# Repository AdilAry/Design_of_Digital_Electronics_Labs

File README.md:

Project for a long range transmitter / reciever.

---
### PCB design requirements;

- No 90 degree trace angles.

- Ground net connected to the copper pour.

- 2 side PCB with several vias connecting them.

- 1 mm and 0.8 mm(in areas where a potential clearence issue might arise.) trace width for the power line.   

- PCB should fit within the Eurocard standard margins 100mm x 160mm.

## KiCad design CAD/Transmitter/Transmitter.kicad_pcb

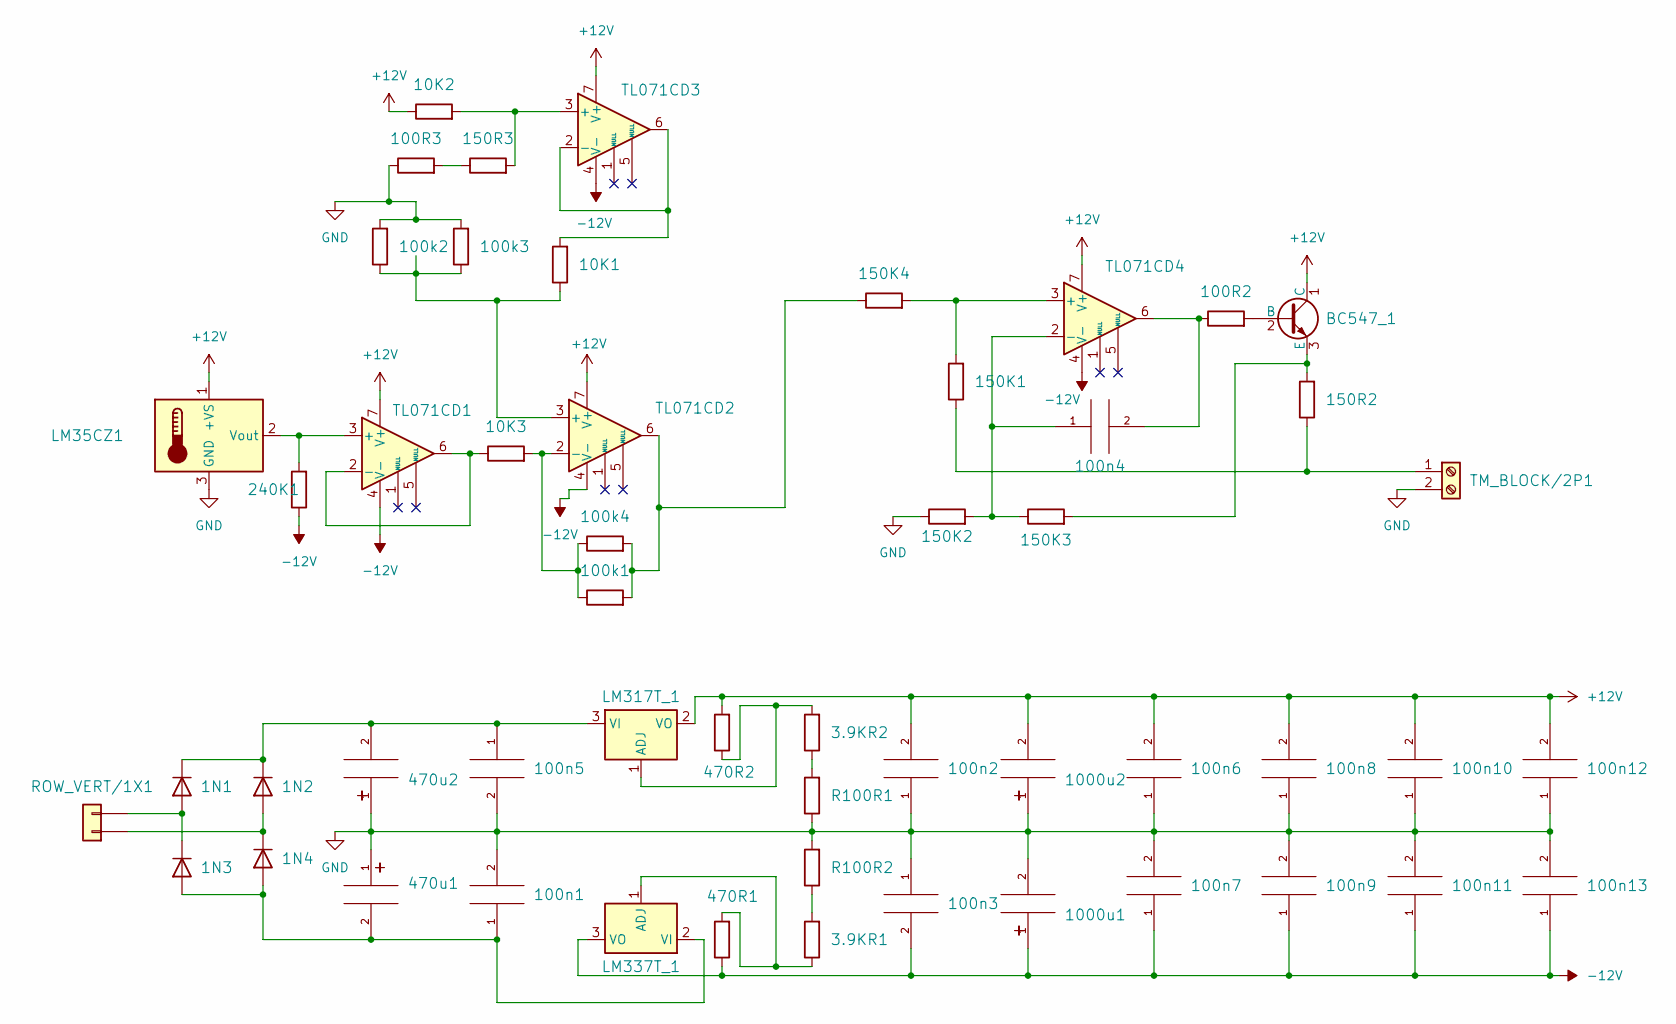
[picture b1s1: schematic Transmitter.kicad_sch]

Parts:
1N1, 1N2, 1N3, 1N4: 1N4007; DO41; Voltage Rating 1000V
3.9KR1, 3.9KR2: 3.9k; 1206; Tolerance +-5%
10K1, 10K2, 10K3: 10k; 1206; Tolerance +-5%
100R2, 100R3: 100R; 1206; Tolerance +-5%
100k1, 100k2, 100k3, 100k4: 100k; 1206; Tolerance +-5%
100n1, 100n2, 100n3, 100n4, 100n5, 100n6, 100n7, 100n8, 100n9, 100n10, 100n11, 100n12, 100n13: 100NF_50V_CER; C1206; Tolerance +-10%
150K1, 150K2, 150K3, 150K4: 150k; 1206; Tolerance +-5%
150R2, 150R3: 150R; 1206; Tolerance +-5%
240K1: 240k; R3_5W; Tolerance +-1%
470R1, 470R2: 470R; 1206; Tolerance +-5%
470u1, 470u2: 470UF_50V_ELE; C_P_5_0_13; Tolerance +-20%
1000u1, 1000u2: 1000UF_50V_ELE; C_P_5_0_13; Tolerance +-20%
BC547_1: BC547_TO92_0.1A; TO-92
LM35CZ1: LM35CZ_TO92; TO-92
LM317T_1: LM317T_TO220_1.5A; TO-220
LM337T_1: LM337T_TO220_1.5A; TO-220
R100R1, R100R2: 100R; 1206; Tolerance +-5%
ROW_VERT/1X1: ROW_VERT_1X2; ROW_VERT_1x2
TL071CD1, TL071CD2, TL071CD3, TL071CD4: TL071CD_SO8; SO8IC
TM_BLOCK/2P1: TM_BLOCK_2P

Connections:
+12V: 10K2.1, 100n2.2, 100n6.2, 100n8.2, 100n10.2, 100n12.2, 470R2.2, 1000u2.2, BC547_1.1 (C), LM35CZ1.1 (+VS), LM317T_1.2 (VO), TL071CD1.7 (V+), TL071CD2.7 (V+), TL071CD3.7 (V+), TL071CD4.7 (V+)
-12V: 100n3.2, 100n7.1, 100n9.1, 100n11.1, 100n13.1, 240K1.1, 470R1.1, 1000u1.1, LM337T_1.3 (VO), TL071CD1.4 (V-), TL071CD2.4 (V-), TL071CD3.4 (V-), TL071CD4.4 (V-)
GND: 100R3.1, 100k2.2, 100k3.2, 100n1.2, 100n2.1, 100n3.1, 100n5.2, 100n6.1, 100n7.2, 100n8.1, 100n9.2, 100n10.1, 100n11.2, 100n12.1, 100n13.2, 150K2.1, 470u1.1, 470u2.1, 1000u1.2, 1000u2.1, LM35CZ1.3 (GND), R100R1.1, R100R2.2, TM_BLOCK/2P1.2
unnamed: 1N1.2 (A), 1N3.1 (K), ROW_VERT/1X1.2
unnamed: 1N1.1 (K), 1N2.1 (K), 100n5.1, 470u2.2, LM317T_1.3 (VI)
unnamed: 1N2.2 (A), 1N4.1 (K), ROW_VERT/1X1.1
unnamed: 1N3.2 (A), 1N4.2 (A), 100n1.1, 470u1.2, LM337T_1.2 (VI)
unnamed: 3.9KR1.2, R100R2.1
unnamed: 3.9KR2.1, R100R1.2
unnamed: 100R2.1, 100n4.2, TL071CD4.6
unnamed: 100R3.2, 150R3.1
unnamed: 100k1.2, 100k4.2, 150K4.1, TL071CD2.6
unnamed: 100R2.2, BC547_1.2 (B)
unnamed: 150K3.2, 150R2.2, BC547_1.3 (E)
unnamed: 240K1.2, LM35CZ1.2 (Vout), TL071CD1.3 (+)
unnamed: 3.9KR2.2, 470R2.1, LM317T_1.1 (ADJ)
unnamed: 3.9KR1.1, 470R1.2, LM337T_1.1 (ADJ)
unnamed: 10K3.1, TL071CD1.2 (-), TL071CD1.6
unnamed: 10K1.1, 100k2.1, 100k3.1, TL071CD2.3 (+)
unnamed: 10K3.2, 100k1.1, 100k4.1, TL071CD2.2 (-)
unnamed: 10K2.2, 150R3.2, TL071CD3.3 (+)
unnamed: 10K1.2, TL071CD3.2 (-), TL071CD3.6
unnamed: 150K1.2, 150K4.2, TL071CD4.3 (+)
unnamed: 100n4.1, 150K2.2, 150K3.1, TL071CD4.2 (-)
unnamed: 150K1.1, 150R2.1, TM_BLOCK/2P1.1

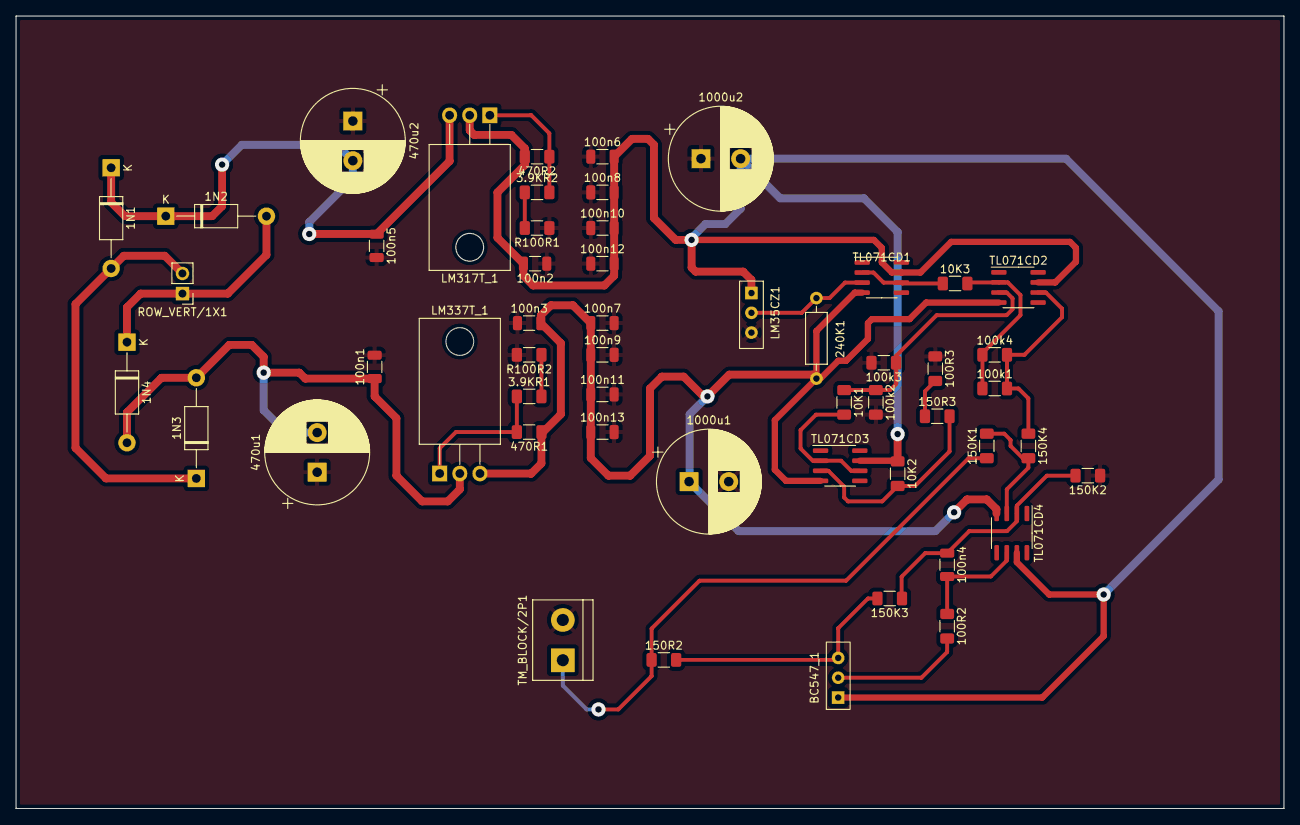
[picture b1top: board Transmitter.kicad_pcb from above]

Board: 2 copper layers, 160.0 x 100.0 mm, 53 parts (0 on the bottom side), 25 nets.

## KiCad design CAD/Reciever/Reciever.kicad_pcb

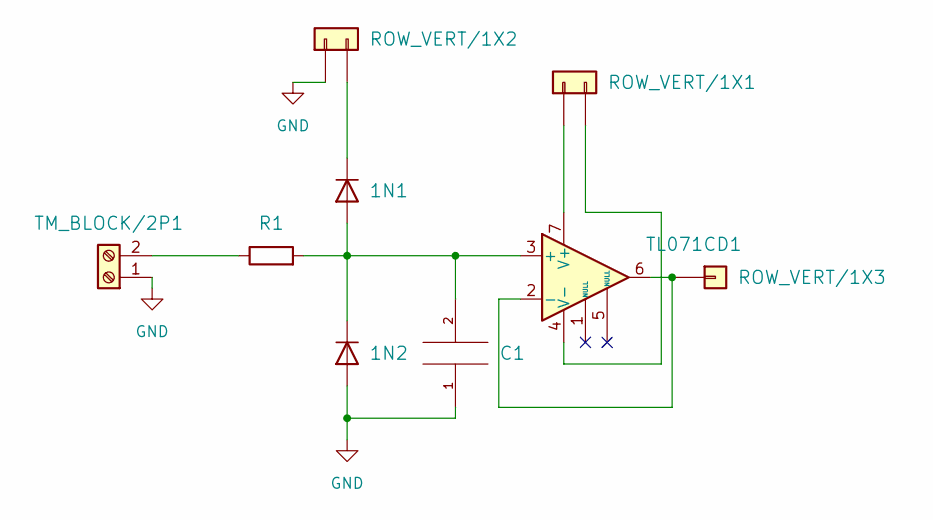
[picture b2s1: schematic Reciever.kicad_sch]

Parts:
1N1, 1N2: 1N4148; DO41; Voltage Rating 75V
C1: 10NF_50V_CER; C1206; Tolerance +-10%
R1: 100R; 1206; Tolerance +-5%
ROW_VERT/1X1, ROW_VERT/1X2: ROW_VERT_1X2; ROW_VERT_1x2
ROW_VERT/1X3: ROW_VERT_1X1; ROW_VERT_1x1
TL071CD1: TL071CD_SO8; SO8IC
TM_BLOCK/2P1: TM_BLOCK_2P

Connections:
GND: 1N2.2 (A), C1.1, ROW_VERT/1X2.1, TM_BLOCK/2P1.1
unnamed: 1N1.2 (A), 1N2.1 (K), C1.2, R1.2, TL071CD1.3 (+)
unnamed: 1N1.1 (K), ROW_VERT/1X2.2
unnamed: ROW_VERT/1X1.1, TL071CD1.7 (V+)
unnamed: ROW_VERT/1X1.2, TL071CD1.4 (V-)
unnamed: ROW_VERT/1X3.1, TL071CD1.2 (-), TL071CD1.6
unnamed: R1.1, TM_BLOCK/2P1.2

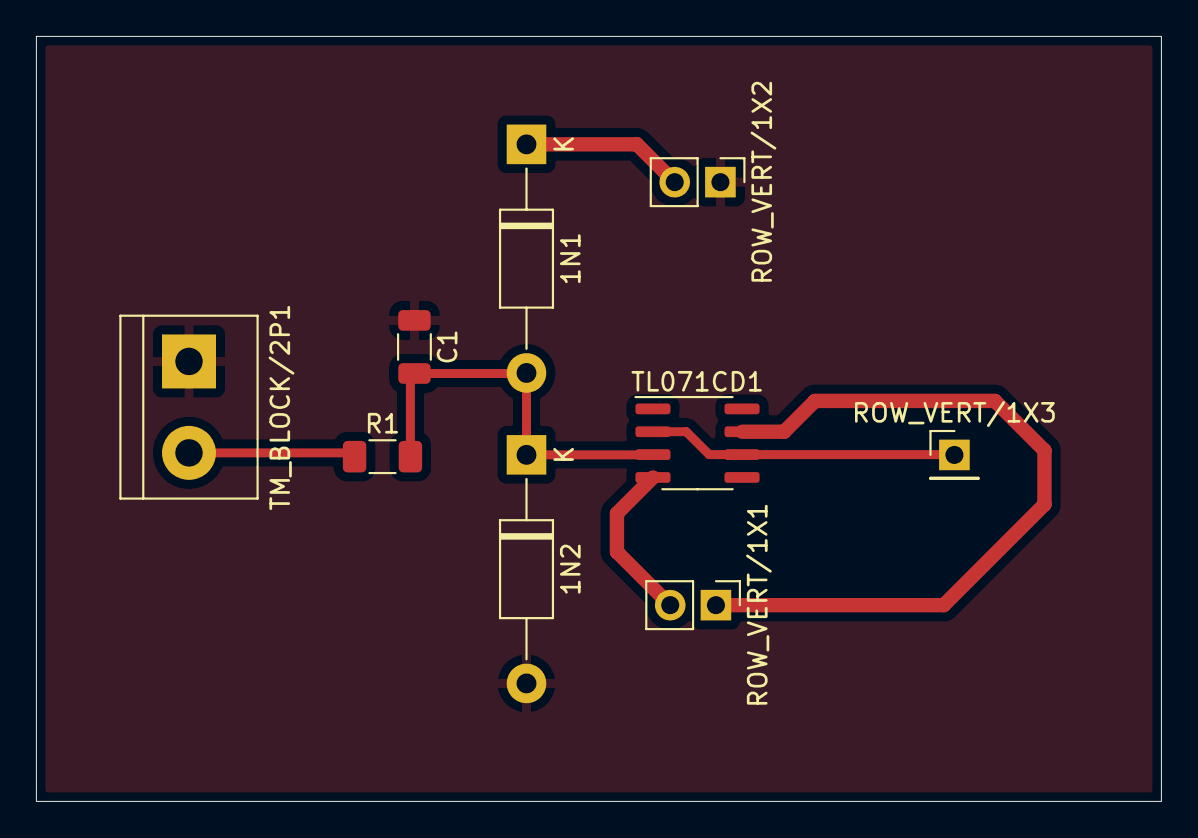
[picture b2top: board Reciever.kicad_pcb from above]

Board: 2 copper layers, 62.5 x 42.5 mm, 9 parts (0 on the bottom side), 7 nets.

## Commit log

2025-09-20 block diagram
2025-09-21 made Reciever CAD
2025-09-21 added archives
2025-09-26 General cleanup, Reciever circuit CAD made
2025-09-27 README added
2025-10-02 PCB adjusted to the Eurocad size standards
2025-10-03 README updated
2025-10-06 some stuff
